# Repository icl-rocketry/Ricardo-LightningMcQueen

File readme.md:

# Ricardo-LightningMcQueen

### Firmware doesn't compile, weird include path error

Removing the '-' from the folder name so it is eg. Ricardo_LightningMcQueen seems to fix this, platformio may be misinterpreting the -L as command/flag

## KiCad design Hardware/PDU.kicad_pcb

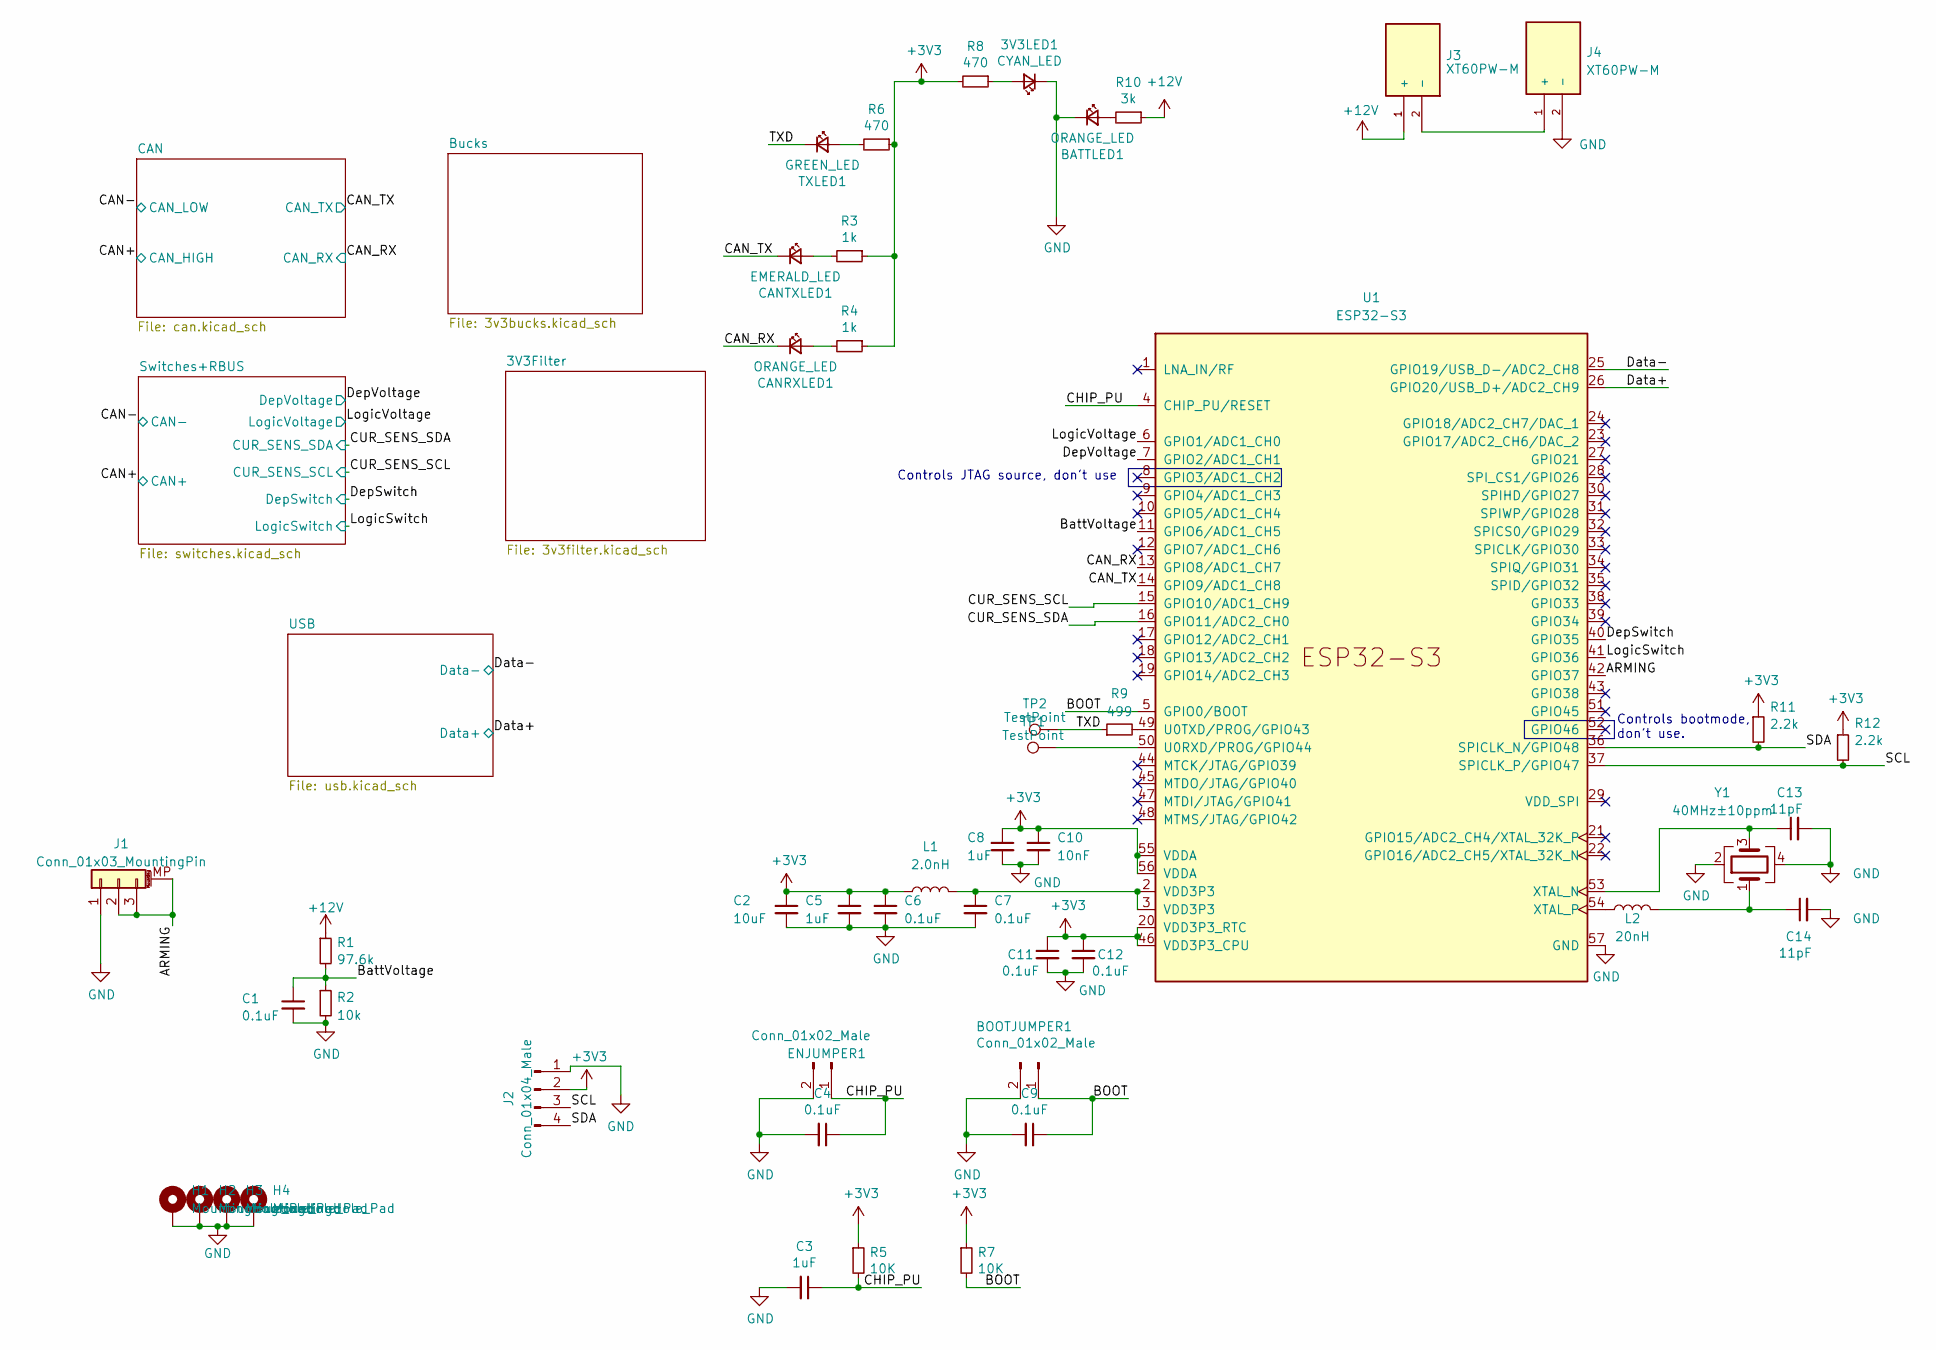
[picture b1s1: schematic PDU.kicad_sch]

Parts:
3V3LED1: CYAN_LED; LED_0402_1005Metric
BATTLED1: ORANGE_LED; LED_0402_1005Metric
BOOTJUMPER1: Conn_01x02_Male; PinHeader_1x02_P2.54mm_Vertical
C1, C4, C6, C7, C9, C11, C12: 0.1uF; C_0402_1005Metric
C2: 10uF; C_0402_1005Metric
C3, C5, C8: 1uF; C_0402_1005Metric
C10: 10nF; C_0402_1005Metric
C13, C14: 11pF; C_0402_1005Metric
CANRXLED1: ORANGE_LED; LED_0402_1005Metric
CANTXLED1: EMERALD_LED; LED_0402_1005Metric
ENJUMPER1: Conn_01x02_Male; PinHeader_1x02_P2.54mm_Vertical
H1, H2, H3, H4: MountingHole_Pad; MountingHole_3.2mm_M3_DIN965_Pad
J1: Conn_01x03_MountingPin; Molex_Nano-Fit_105313-xx02_1x02_P2.50mm_Horizontal
J2: Conn_01x04_Male; PinHeader_1x04_P2.54mm_Vertical
J3, J4: XT60PW-M; AMASS_XT60PW-M; PARTREV V1.2
L1: 2.0nH; L_0402_1005Metric
L2: 20nH; L_0402_1005Metric
R1: 97.6k; R_0402_1005Metric
R2: 10k; R_0402_1005Metric
R3, R4: 1k; R_0402_1005Metric
R5, R7: 10K; R_0402_1005Metric
R6, R8: 470; R_0402_1005Metric
R9: 499; R_0402_1005Metric
R10: 3k; R_0402_1005Metric
R11, R12: 2.2k; R_0402_1005Metric
TP1, TP2: TestPoint; TestPoint_Pad_D1.0mm
TXLED1: GREEN_LED; LED_0402_1005Metric
U1: ESP32-S3; QFN40P700X700X90-57N
Y1: 40MHz±10ppm; Crystal_SMD_2016-4Pin_2.0x1.6mm

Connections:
+3V3: C2.1, C5.1, C6.1, C8.1, C10.1, C11.1, C12.1, J2.2, L1.1, R3.1, R4.1, R5.1, R6.1, R7.1, R8.2, R11.1, R12.1, U1.20 (VDD3P3_RTC), U1.46 (VDD3P3_CPU), U1.55 (VDDA), U1.56 (VDDA); also elsewhere on the board
+12V: J3.1 (+), R1.1, R10.1; also elsewhere on the board
/ARMING: J1.2, J1.3, J1.MP (MountPin), U1.42 (GPIO37)
/BOOT: BOOTJUMPER1.1, C9.1, R7.2, U1.5 (GPIO0/BOOT)
/BattVoltage: C1.1, R1.2, R2.1, U1.11 (GPIO6/ADC1_CH5)
/CAN_RX: CANRXLED1.1 (K), U1.13 (GPIO8/ADC1_CH7); also elsewhere on the board
/CAN_TX: CANTXLED1.1 (K), U1.14 (GPIO9/ADC1_CH8); also elsewhere on the board
/CHIP_PU: C3.1, C4.1, ENJUMPER1.1, R5.2, U1.4 (CHIP_PU/RESET)
/CUR_SENS_SCL: U1.15 (GPIO10/ADC1_CH9); also elsewhere on the board
/CUR_SENS_SDA: U1.16 (GPIO11/ADC2_CH0); also elsewhere on the board
/Data+: U1.26 (GPIO20/USB_D+/ADC2_CH9); also elsewhere on the board
/Data-: U1.25 (GPIO19/USB_D-/ADC2_CH8); also elsewhere on the board
/DepSwitch: U1.40 (GPIO35); also elsewhere on the board
/DepVoltage: U1.7 (GPIO2/ADC1_CH1); also elsewhere on the board
/LogicSwitch: U1.41 (GPIO36); also elsewhere on the board
/LogicVoltage: U1.6 (GPIO1/ADC1_CH0); also elsewhere on the board
/SCL: J2.3, R12.2, U1.37 (SPICLK_P/GPIO47)
/SDA: J2.4, R11.2, U1.36 (SPICLK_N/GPIO48)
/TXD: R9.1, TP2.1, TXLED1.1 (K)
GND: 3V3LED1.1 (K), BATTLED1.1 (K), BOOTJUMPER1.2, C1.2, C2.2, C3.2, C4.2, C5.2, C6.2, C7.2, C8.2, C9.2, C10.2, C11.2, C12.2, C13.2, C14.2, ENJUMPER1.2, H1.1, H2.1, H3.1, H4.1, J1.1, J2.1, J4.2 (-), R2.2, U1.57 (GND), Y1.2, Y1.4; also elsewhere on the board
unnamed: 3V3LED1.2 (A), R8.1
unnamed: BATTLED1.2 (A), R10.2
unnamed: C7.1, L1.2, U1.2 (VDD3P3), U1.3 (VDD3P3)
unnamed: C14.1, L2.2, Y1.1
unnamed: CANRXLED1.2 (A), R4.2
unnamed: CANTXLED1.2 (A), R3.2
unnamed: J3.2 (-), J4.1 (+)
unnamed: R6.2, TXLED1.2 (A)
unnamed: TP1.1, U1.50 (U0RXD/PROG/GPIO44)
unnamed: R9.2, U1.49 (U0TXD/PROG/GPIO43)
unnamed: C13.1, U1.53 (XTAL_N), Y1.3
unnamed: L2.1, U1.54 (XTAL_P)

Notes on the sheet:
Controls JTAG source, don't use
Controls bootmode, don't use.

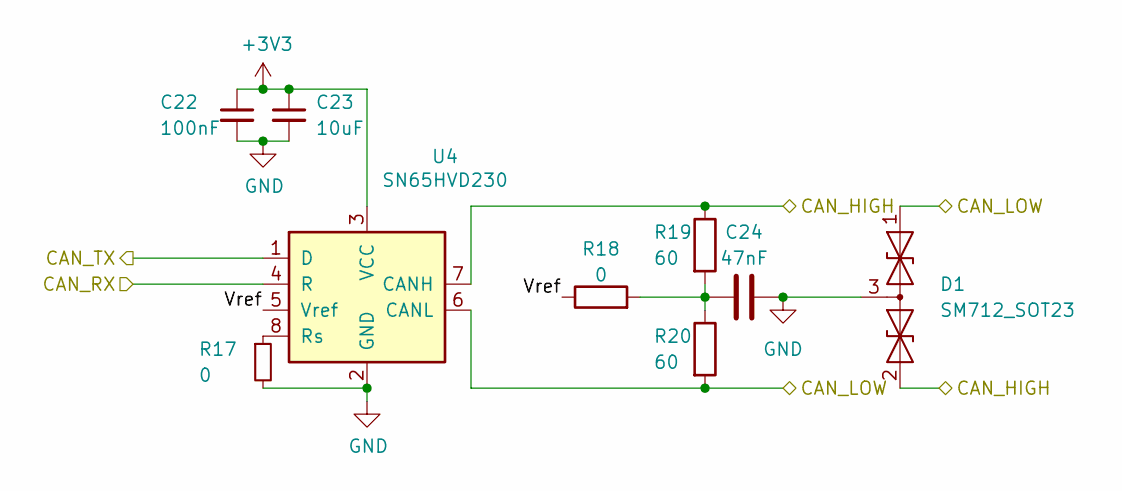
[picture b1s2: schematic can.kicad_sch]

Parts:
C22: 100nF; C_0402_1005Metric
C23: 10uF; C_0402_1005Metric
C24: 47nF; C_0402_1005Metric
D1: SM712_SOT23; SOT-23
R17: 0; R_0603_1608Metric
R18: 0; R_0402_1005Metric
R19, R20: 60; R_0603_1608Metric
U4: SN65HVD230; SOIC-8_3.9x4.9mm_P1.27mm

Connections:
+3V3: C22.1, C23.1, U4.3 (VCC); also elsewhere on the board
/CAN+: D1.2 (A2), R19.1, U4.7 (CANH); also elsewhere on the board
/CAN-: D1.1 (A1), R20.2, U4.6 (CANL); also elsewhere on the board
/CAN/Vref: R18.1, U4.5 (Vref)
/CAN_RX: U4.4 (R); also elsewhere on the board
/CAN_TX: U4.1 (D); also elsewhere on the board
GND: C22.2, C23.2, C24.2, D1.3 (common), R17.2, U4.2 (GND); also elsewhere on the board
unnamed: C24.1, R18.2, R19.2, R20.1
unnamed: R17.1, U4.8 (Rs)

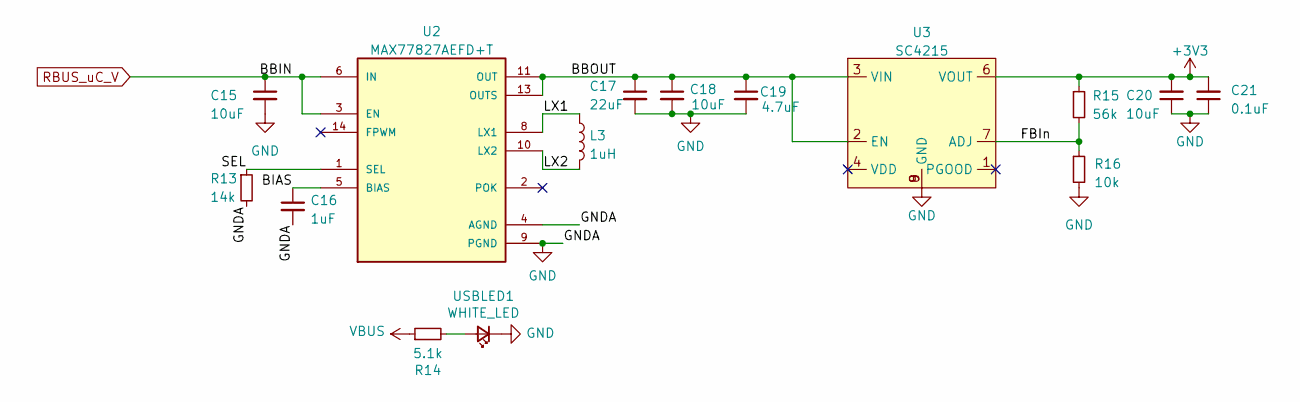
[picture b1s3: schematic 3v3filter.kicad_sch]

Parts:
C15: 10uF; C_0603_1608Metric
C16: 1uF; C_0402_1005Metric
C17: 22uF; C_0603_1608Metric
C18, C20: 10uF; C_0402_1005Metric
C19: 4.7uF; C_0402_1005Metric
C21: 0.1uF; C_0402_1005Metric
L3: 1uH; L_0805_2012Metric
R13: 14k; R_0402_1005Metric
R14: 5.1k; R_0402_1005Metric
R15: 56k; R_0402_1005Metric
R16: 10k; R_0402_1005Metric
U2: MAX77827AEFD+T; CONV_MAX77827AEFD+T; PARTREV B
U3: SC4215; SOIC127P599X175-9N
USBLED1: WHITE_LED; LED_0402_1005Metric

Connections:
+3V3: C20.2, C21.2, R15.1, U3.6 (VOUT); also elsewhere on the board
/3V3Filter/BBOUT: C17.1, C18.1, C19.1, U2.11 (OUT), U2.13 (OUTS), U3.2 (EN), U3.3 (VIN)
/3V3Filter/BIAS: C16.1, U2.5 (BIAS)
/3V3Filter/FBIn: R15.2, R16.1, U3.7 (ADJ)
/3V3Filter/LX1: L3.1, U2.8 (LX1)
/3V3Filter/LX2: L3.2, U2.10 (LX2)
/3V3Filter/SEL: R13.1, U2.1 (SEL)
GND: C15.2, C16.2, C17.2, C18.2, C19.2, C20.1, C21.1, R13.2, R16.2, U2.4 (AGND), U2.9 (PGND), U3.8 (GND), U3.9 (GND), USBLED1.1 (K); also elsewhere on the board
unnamed: R14.2, USBLED1.2 (A)
RBUS_uC_V: C15.1, U2.3 (EN), U2.6 (IN); also elsewhere on the board
VBUS: R14.1; also elsewhere on the board

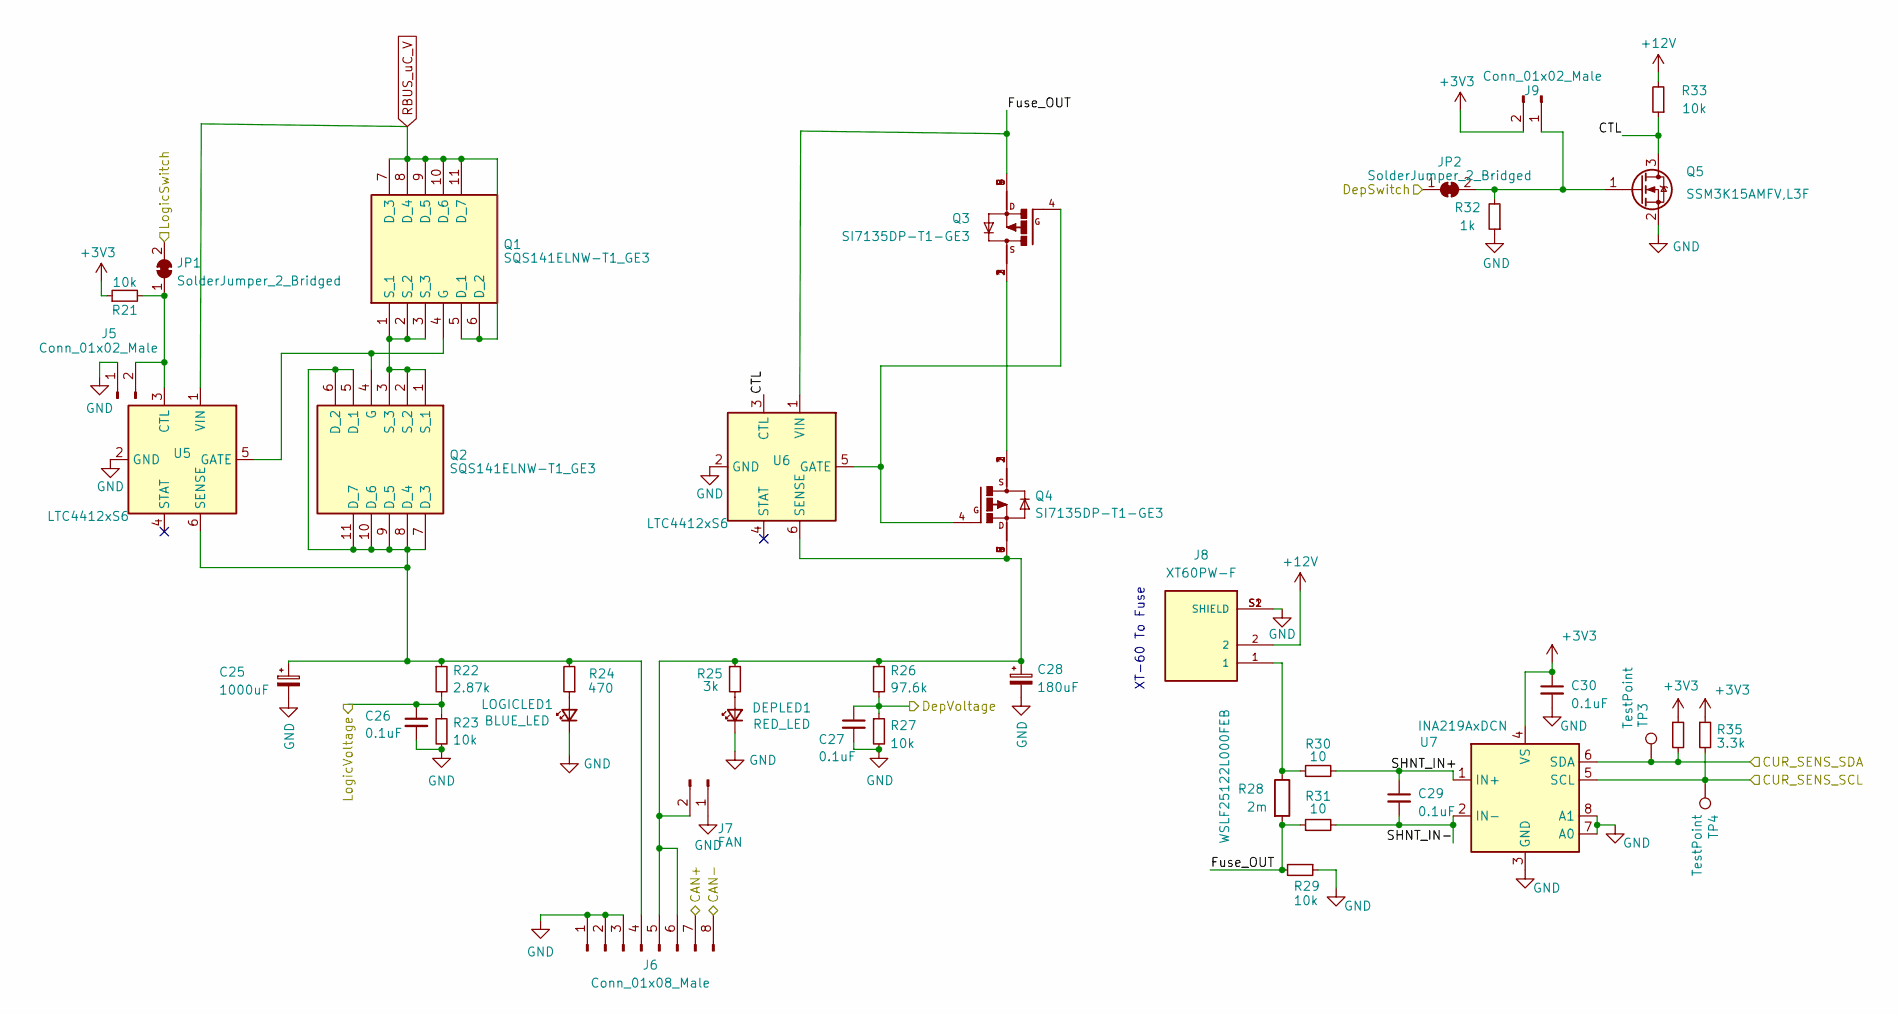
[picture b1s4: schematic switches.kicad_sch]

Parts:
C25: 1000uF; CP_Elec_10x10
C26, C29, C30: 0.1uF; C_0402_1005Metric
C27: 0.1uF; C_0402_1005Metric; MPN CGA0603X5R226M160JT
C28: 180uF; CP_Elec_10x10; MPN VKME1301H181MV
DEPLED1: RED_LED; LED_0402_1005Metric
J5, J9: Conn_01x02_Male; PinHeader_1x02_P2.54mm_Vertical
J6: Conn_01x08_Male; Molex_Mini-Fit_Jr_5569-08A2_2x04_P4.20mm_Horizontal
J7: FAN; PinHeader_1x02_P2.54mm_Vertical
J8: XT60PW-F; AMASS_XT60PW-F; PARTREV V1.2
JP1, JP2: SolderJumper_2_Bridged; SolderJumper-2_P1.3mm_Bridged_RoundedPad1.0x1.5mm
LOGICLED1: BLUE_LED; LED_0402_1005Metric
Q1, Q2: SQS141ELNW-T1_GE3; SQS850ENT1_GE3; Manufacturer_Part_Number SQS141ELNW-T1_GE3; Mouser Part Number 78-SQS141ELNW-T1_GE3
Q3, Q4: SI7135DP-T1-GE3; PowerPAK_SO-8_Single
Q5: SSM3K15AMFV,L3F; SOT-723; MPN SSM3K15AMFV,L3F(T
R21, R23, R27, R29, R33: 10k; R_0402_1005Metric
R22: 2.87k; R_0402_1005Metric
R24: 470; R_0402_1005Metric
R25: 3k; R_0402_1005Metric
R26: 97.6k; R_0402_1005Metric
R28: 2m; R_2512_6332Metric_Pad1.40x3.35mm_HandSolder; MPN WSLF25122L000FEB
R30, R31: 10; R_0402_1005Metric
R32: 1k; R_0402_1005Metric
R34, R35: 3.3k; R_0402_1005Metric
TP3, TP4: TestPoint; TestPoint_Pad_D1.0mm
U5, U6: LTC4412xS6; TSOT-23-6
U7: INA219AxDCN; SOT-23-8

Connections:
+3V3: C30.1, J9.2, R21.1, R34.1, R35.1, U7.4 (VS); also elsewhere on the board
+12V: J8.2, R33.2; also elsewhere on the board
/CAN+: J6.7; also elsewhere on the board
/CAN-: J6.8; also elsewhere on the board
/CUR_SENS_SCL: R35.2, TP4.1, U7.5 (SCL); also elsewhere on the board
/CUR_SENS_SDA: R34.2, TP3.1, U7.6 (SDA); also elsewhere on the board
/DepSwitch: JP2.1 (A); also elsewhere on the board
/DepVoltage: C27.1, R26.2, R27.1; also elsewhere on the board
/LogicSwitch: JP1.2 (B); also elsewhere on the board
/LogicVoltage: C26.1, R22.2, R23.1; also elsewhere on the board
/Switches+RBUS/CTL: Q5.3 (D), R33.1, U6.3 (CTL)
/Switches+RBUS/Fuse_OUT: Q3.5, Q3.6, Q3.7, Q3.8, Q3.9, R28.2, R29.2, R31.1, U6.1 (VIN)
/Switches+RBUS/SHNT_IN+: C29.1, R30.2, U7.1 (IN+)
/Switches+RBUS/SHNT_IN-: C29.2, R31.2, U7.2 (IN-)
GND: C25.2, C26.2, C27.2, C28.2, C30.2, DEPLED1.1 (K), J5.1, J6.1, J6.2, J6.3, J7.1, J8.S1 (SHIELD), J8.S2 (SHIELD), LOGICLED1.1 (K), Q5.2 (S), R23.2, R27.2, R29.1, R32.1, U5.2 (GND), U6.2 (GND), U7.3 (GND), U7.7 (A0), U7.8 (A1); also elsewhere on the board
unnamed: DEPLED1.2 (A), R25.2
unnamed: J5.2, JP1.1 (A), R21.2, U5.3 (CTL)
unnamed: C25.1, J6.4, Q2.5 (D_1), Q2.6 (D_2), Q2.7 (D_3), Q2.8 (D_4), Q2.9 (D_5), Q2.10 (D_6), Q2.11 (D_7), R22.1, R24.2, U5.6 (SENSE)
unnamed: C28.1, J6.5, J6.6, J7.2, Q4.5, Q4.6, Q4.7, Q4.8, Q4.9, R25.1, R26.1, U6.6 (SENSE)
unnamed: J8.1, R28.1, R30.1
unnamed: J9.1, JP2.2 (B), Q5.1 (G), R32.2
unnamed: LOGICLED1.2 (A), R24.1
unnamed: Q1.4 (G), Q2.4 (G), U5.5 (GATE)
unnamed: Q1.1 (S_1), Q1.2 (S_2), Q1.3 (S_3), Q2.1 (S_1), Q2.2 (S_2), Q2.3 (S_3)
unnamed: Q3.1, Q3.2, Q3.3, Q4.1, Q4.2, Q4.3
unnamed: Q3.4, Q4.4, U6.5 (GATE)
RBUS_uC_V: Q1.5 (D_1), Q1.6 (D_2), Q1.7 (D_3), Q1.8 (D_4), Q1.9 (D_5), Q1.10 (D_6), Q1.11 (D_7), U5.1 (VIN); also elsewhere on the board

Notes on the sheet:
XT-60 To Fuse

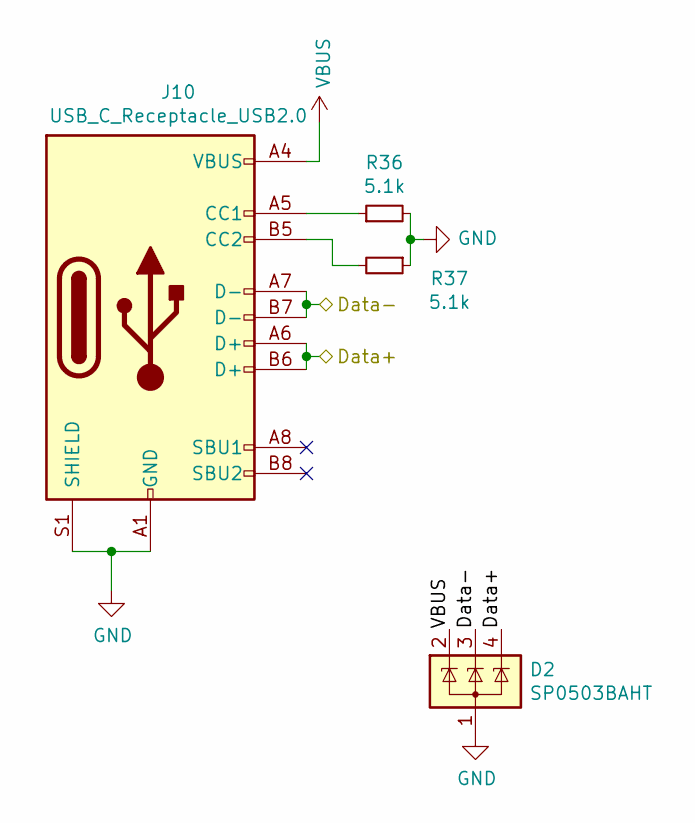
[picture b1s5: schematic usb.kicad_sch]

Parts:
D2: SP0503BAHT; SOT-143
J10: USB_C_Receptacle_USB2.0; USB_C_Receptacle_Palconn_UTC16-G
R36, R37: 5.1k; R_0402_1005Metric

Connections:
/Data+: D2.4 (K), J10.A6 (D+), J10.B6 (D+); also elsewhere on the board
/Data-: D2.3 (K), J10.A7 (D-), J10.B7 (D-); also elsewhere on the board
GND: D2.1 (A), J10.A1 (GND), J10.A12 (GND), J10.B1 (GND), J10.B12 (GND), J10.S1 (SHIELD), R36.2, R37.1; also elsewhere on the board
unnamed: J10.A5 (CC1), R36.1
unnamed: J10.B5 (CC2), R37.2
VBUS: D2.2 (K), J10.A4 (VBUS), J10.A9 (VBUS), J10.B4 (VBUS), J10.B9 (VBUS); also elsewhere on the board

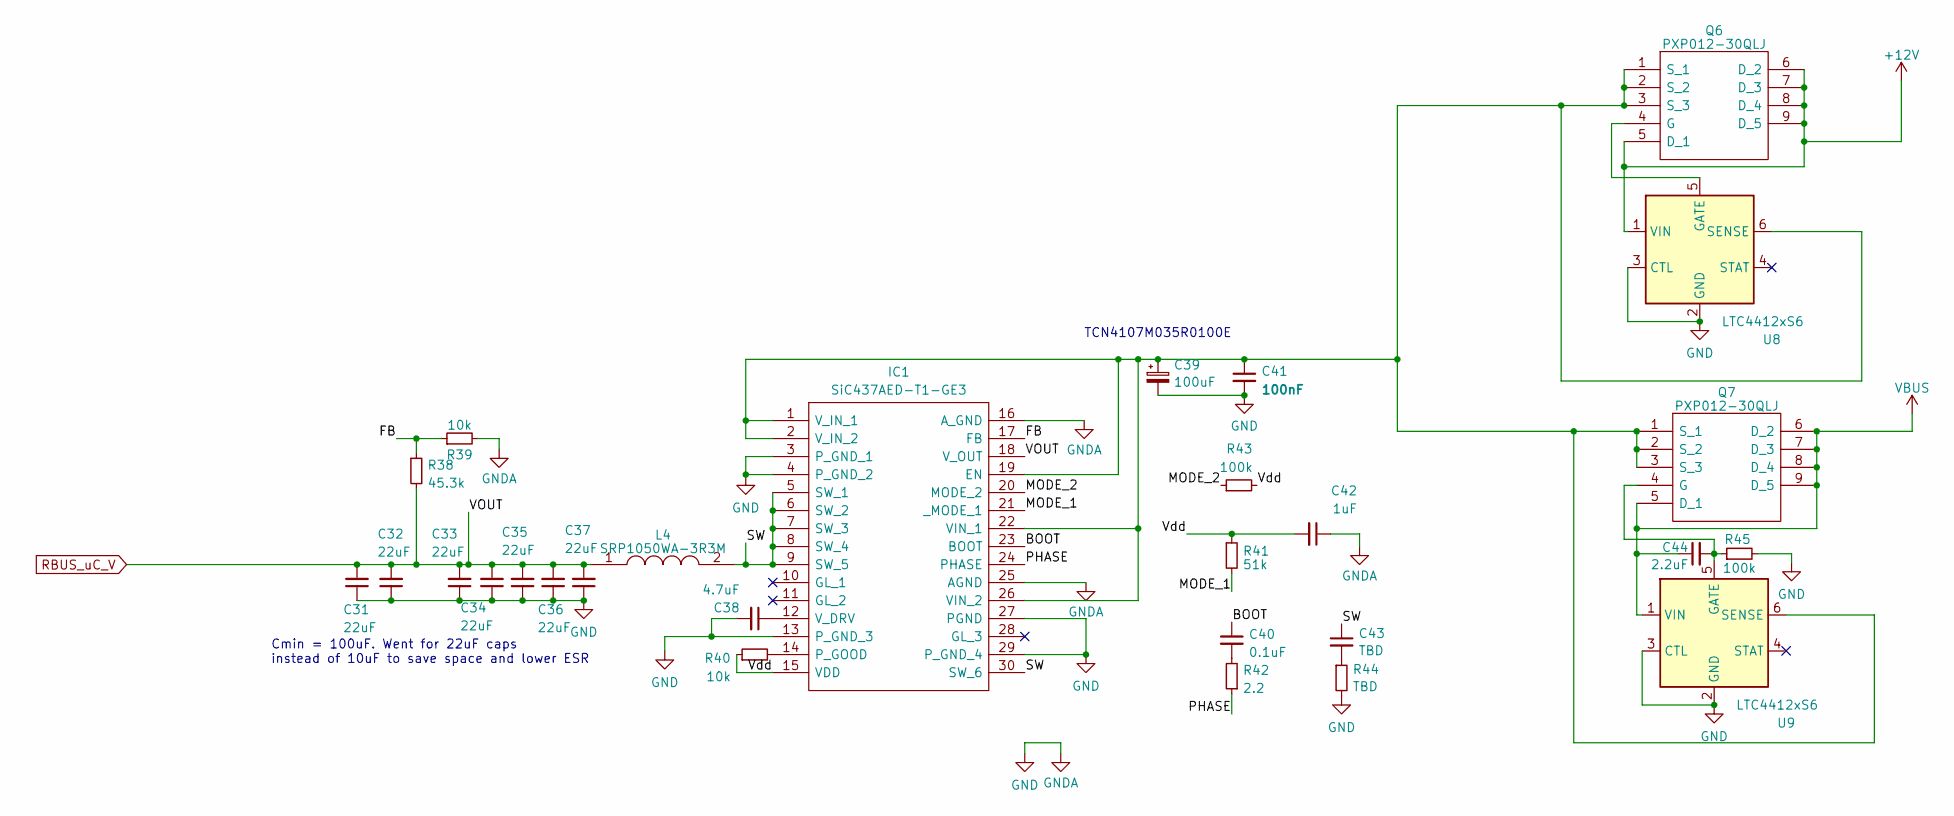
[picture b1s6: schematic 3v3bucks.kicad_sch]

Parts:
C31, C32, C33, C34, C35, C36, C37: 22uF; C_0603_1608Metric; MPN CGA0603X5R226M160JT
C38: 4.7uF; C_0402_1005Metric
C39: 100uF; CAPPM7362X200N
C40: 0.1uF; C_0402_1005Metric
C41: 100nF; C_0603_1608Metric; MPN C1005X7R1H104KT000S
C42: 1uF; C_0402_1005Metric
C43: TBD; C_0603_1608Metric
C44: 2.2uF; C_0402_1005Metric
IC1: SiC437AED-T1-GE3; SiC437BEDT1GE3; Manufacturer_Part_Number SiC437BED-T1-GE3; Mouser Part Number 78-SIC437BED-T1-GE3
L4: SRP1050WA-3R3M; INDPM110100X540N; Manufacturer_Part_Number SRP1050WA-3R3M
Q6, Q7: PXP012-30QLJ; PXP01230QLJ; Manufacturer_Part_Number PXP012-30QLJ; Mouser Part Number 771-PXP012-30QLJ
R38: 45.3k; R_0402_1005Metric
R39, R40: 10k; R_0402_1005Metric
R41: 51k; R_0402_1005Metric
R42: 2.2; R_0402_1005Metric
R43, R45: 100k; R_0402_1005Metric
R44: TBD; R_0603_1608Metric
U8, U9: LTC4412xS6; TSOT-23-6

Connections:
+12V: Q6.5 (D_1), Q6.6 (D_2), Q6.7 (D_3), Q6.8 (D_4), Q6.9 (D_5), U8.1 (VIN); also elsewhere on the board
/Bucks/BOOT: C40.1, IC1.23 (BOOT)
/Bucks/FB: IC1.17 (FB), R38.1, R39.1
/Bucks/MODE_1: IC1.21 (_MODE_1), R41.2
/Bucks/MODE_2: IC1.20 (MODE_2), R43.1
/Bucks/PHASE: IC1.24 (PHASE), R42.1
/Bucks/SW: C43.1, IC1.5 (SW_1), IC1.6 (SW_2), IC1.7 (SW_3), IC1.8 (SW_4), IC1.9 (SW_5), IC1.30 (SW_6), L4.2
/Bucks/Vdd: C42.2, IC1.15 (VDD), R40.1, R41.1, R43.2
GND: C31.1, C32.1, C33.1, C34.1, C35.1, C36.1, C37.1, C38.2, C39.2, C41.2, C42.1, IC1.3 (P_GND_1), IC1.4 (P_GND_2), IC1.13 (P_GND_3), IC1.16 (A_GND), IC1.25 (AGND), IC1.27 (PGND), IC1.29 (P_GND_4), R39.2, R44.2, R45.2, U8.2 (GND), U8.3 (CTL), U9.2 (GND), U9.3 (CTL); also elsewhere on the board
unnamed: C40.2, R42.2
unnamed: C43.2, R44.1
unnamed: C39.1, C41.1, IC1.1 (V_IN_1), IC1.2 (V_IN_2), IC1.19 (EN), IC1.22 (VIN_1), IC1.26 (VIN_2), Q6.1 (S_1), Q6.2 (S_2), Q6.3 (S_3), Q7.1 (S_1), Q7.2 (S_2), Q7.3 (S_3), U8.6 (SENSE), U9.6 (SENSE)
unnamed: IC1.14 (P_GOOD), R40.2
unnamed: C38.1, IC1.12 (V_DRV)
unnamed: Q6.4 (G), U8.5 (GATE)
unnamed: C44.2, Q7.4 (G), R45.1, U9.5 (GATE)
RBUS_uC_V: C31.2, C32.2, C33.2, C34.2, C35.2, C36.2, C37.2, IC1.18 (V_OUT), L4.1, R38.2; also elsewhere on the board
VBUS: C44.1, Q7.5 (D_1), Q7.6 (D_2), Q7.7 (D_3), Q7.8 (D_4), Q7.9 (D_5), U9.1 (VIN); also elsewhere on the board

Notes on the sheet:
TCN4107M035R0100E
Cmin = 100uF. Went for 22uF caps instead of 10uF to save space and lower ESR

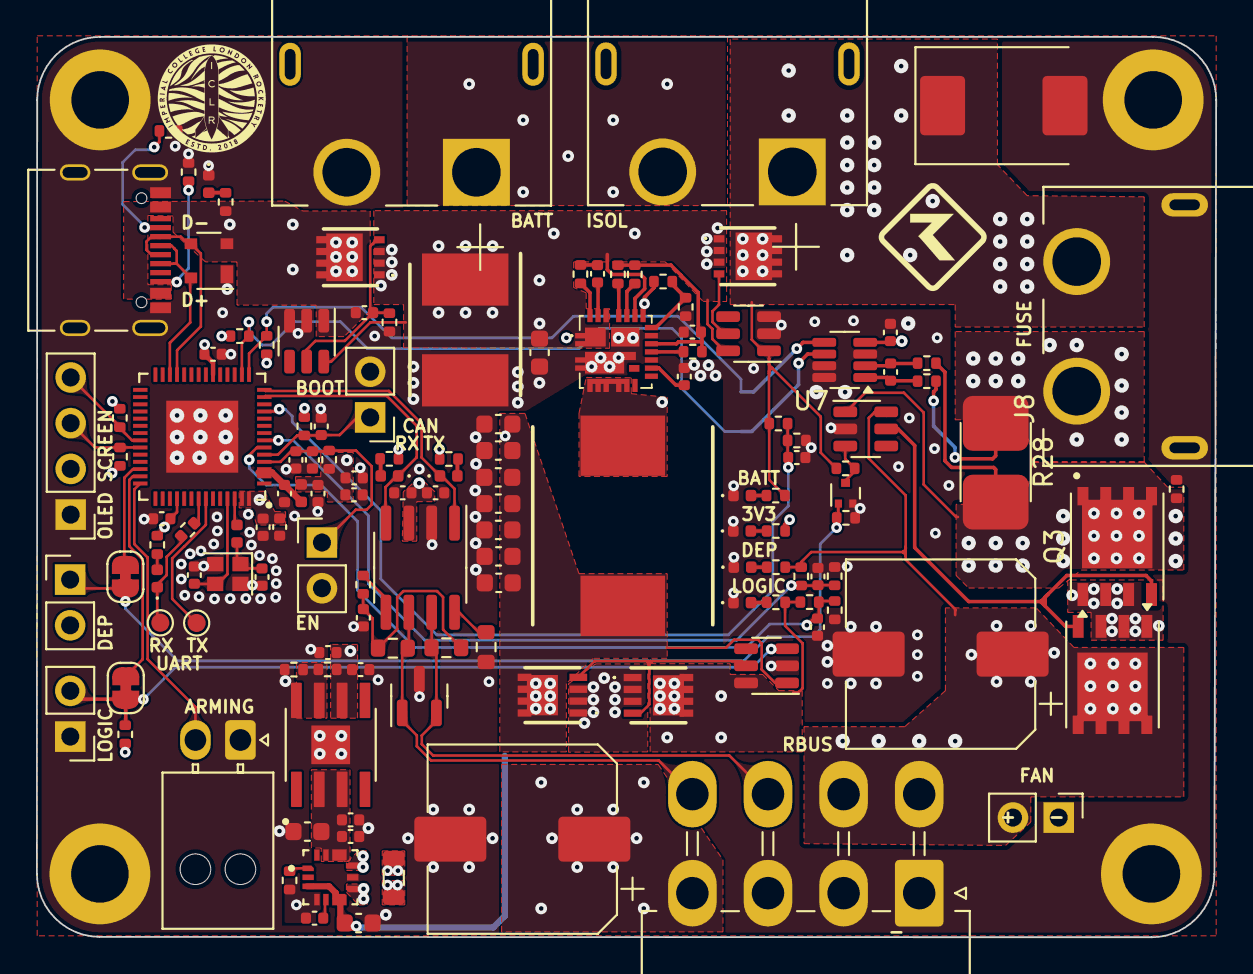
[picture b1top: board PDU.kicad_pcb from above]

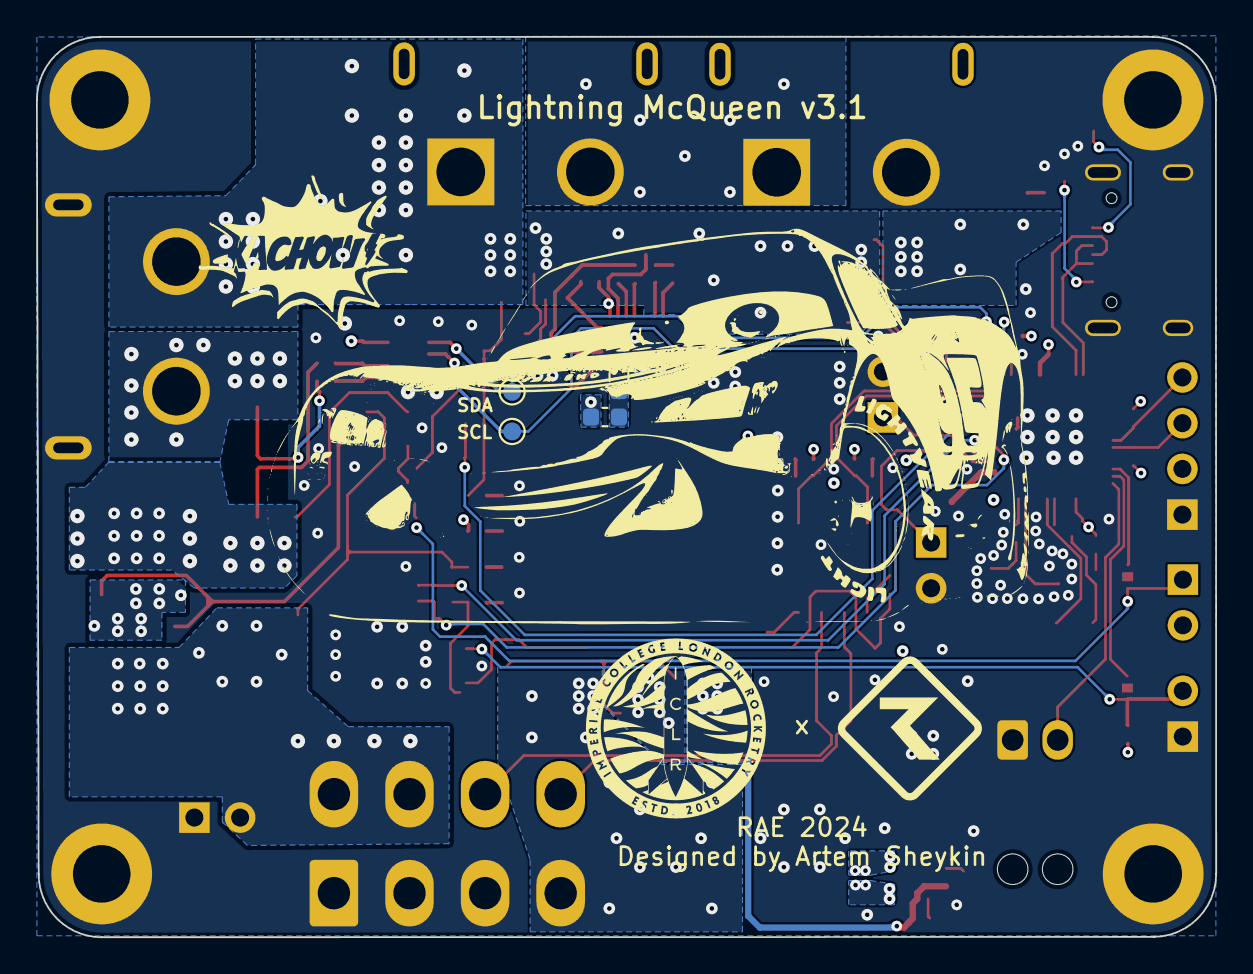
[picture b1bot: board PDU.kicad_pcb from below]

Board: 4 copper layers, 65.5 x 50.0 mm, 144 parts (4 on the bottom side), 77 nets.

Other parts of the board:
D4: SMCJ24AHE3_A/H; D_SMC

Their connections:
+12V: D4.1 (K); also elsewhere on the board
GND: D4.2 (A); also elsewhere on the board

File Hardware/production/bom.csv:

Designator,Footprint,Quantity,Value,LCSC Part #
3V3LED1,0402,1,CYAN_LED,
"BATTLED1, CANRXLED1",0402,2,ORANGE_LED,
"BOOTJUMPER1, ENJUMPER1, J5, J9",PinHeader_1x02_P2.54mm_Vertical,4,Conn_01x02_Male,
"C1, C11, C12, C21, C26, C29, C30, C4, C40, C6, C7, C9",0402,12,0.1uF,
C10,0402,1,10nF,
"C13, C14",0402,2,11pF,
C15,0603,1,10uF,
"C16, C3, C42, C5, C8",0402,5,1uF,
C17,0603,1,22uF,
"C18, C2, C20, C23",0402,4,10uF,
"C19, C38",0402,2,4.7uF,
C22,0402,1,100nF,
C24,0402,1,47nF,
C25,CP_Elec_10x10,1,1000uF,
C27,0402,1,0.1uF,CGA0603X5R226M160JT
C28,CP_Elec_10x10,1,180uF,VKME1301H181MV
"C31, C32, C33, C34, C35, C36, C37",0603,7,22uF, CGA0603X5R226M160JT
C39,CAPPM7362X200N,1,100uF,
C41,0603,1,100nF, C1005X7R1H104KT000S
"C43, R44",0603,2,TBD,
C44,0402,1,2.2uF,
CANTXLED1,0402,1,EMERALD_LED,
D1,SOT-23,1,SM712_SOT23,
D2,SOT-143,1,SP0503BAHT,
D4,D_SMC,1,SMCJ24AHE3_A/H,
DEPLED1,0402,1,RED_LED,
"H1, H2, H3, H4",MountingHole_3.2mm_M3_DIN965_Pad,4,MountingHole_Pad,
IC1,SiC437BEDT1GE3,1,SiC437AED-T1-GE3, SIC437AED-T1-GE3
J1,Molex_Nano-Fit_105313-xx02_1x02_P2.50mm_Horizontal,1,Conn_01x03_MountingPin,
J10,USB_C_Receptacle_Palconn_UTC16-G,1,USB_C_Receptacle_USB2.0,
J2,PinHeader_1x04_P2.54mm_Vertical,1,Conn_01x04_Male,
"J3, J4",AMASS_XT60PW-M,2,XT60PW-M,
J6,Molex_Mini-Fit_Jr_5569-08A2_2x04_P4.20mm_Horizontal,1,Conn_01x08_Male,
J7,PinHeader_1x02_P2.54mm_Vertical,1,FAN,
J8,AMASS_XT60PW-F,1,XT60PW-F,
"JP1, JP2",SolderJumper-2_P1.3mm_Bridged_RoundedPad1.0x1.5mm,2,SolderJumper_2_Bridged,
L1,0402,1,2.0nH,
L2,0402,1,20nH,
L3,0805,1,1uH,
L4,INDPM110100X540N,1,SRP1050WA-3R3M,
LOGICLED1,0402,1,BLUE_LED,
"Q1, Q2",SQS850ENT1_GE3,2,SQS141ELNW-T1_GE3,
"Q3, Q4",PowerPAK_SO-8_Single,2,SI7635DP-T1-GE3,
Q5,SOT-723,1,"SSM3K15AMFV,L3F","SSM3K15AMFV,L3F(T"
"Q6, Q7",PXP01230QLJ,2,PXP012-30QLJ,
"R1, R26",0402,2,97.6k,
"R10, R25",0402,2,3k,
"R11, R12",0402,2,2.2k,
R13,0402,1,14k,
"R14, R36, R37",0402,3,5.1k,
R15,0402,1,56k,
"R16, R2, R21, R23, R27, R29, R33, R39, R40, R5, R7",0402,11,10k,
R17,0603,1,0,
R18,0402,1,0,
"R19, R20",0603,2,60,
R22,0402,1,2.87k,
"R24, R6, R8",0402,3,470,
R28,2512,1,2m,WSLF25122L000FEB
"R3, R32, R4",0402,3,1k,
"R30, R31",0402,2,10,
"R34, R35",0402,2,3.3k,
R38,0402,1,45.3k,
R41,0402,1,51k,
R42,0402,1,2.2,
"R43, R45",0402,2,100k,
R9,0402,1,499,
"TP1, TP2, TP3, TP4",TestPoint_Pad_D1.0mm,4,TestPoint,
TXLED1,0402,1,GREEN_LED,
U1,QFN40P700X700X90-57N,1,ESP32-S3,
U2,CONV_MAX77827AEFD+T,1,MAX77827AEFD+T,
U3,SOIC127P599X175-9N,1,SC4215,
U4,SOIC-8_3.9x4.9mm_P1.27mm,1,SN65HVD230,
"U5, U6, U8, U9",TSOT-23-6,4,LTC4412xS6,
U7,SOT-23-8,1,INA219AxDCN,
USBLED1,0402,1,WHITE_LED,
Y1,Crystal_SMD_2016-4Pin_2.0x1.6mm,1,40MHz±10ppm,
